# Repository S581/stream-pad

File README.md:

# Steampad ⌨️

**Steampad** is a high-performance 4x4 macropad featuring a rotary encoder and full per-key RGB lighting. Powered by the **Seeed Studio XIAO RP2040**, it is designed for maximum productivity and customization using **QMK Firmware** and the **VIAL** protocol.

---

## Features
* **16 Mechanical Keys:** A full 4x4 grid for macros, shortcuts, and numpad use.
* **Rotary Encoder:** EC11 encoder for precision volume control, scrolling, or scrubbing.
* **Per-Key RGB:** 16 integrated SK6812 Mini-E LEDs for vibrant, customizable lighting.
* **VIAL Support:** Change your keymap and macros in real-time via the VIAL web or desktop app—no code editing required after flashing.
* **RP2040 Power:** Utilizes the RP2040's PIO state machines for perfect LED timing and ultra-low latency.

---

## Hardware Overview
The Steampad uses a matrix circuit with a **COL2ROW** diode orientation, ensuring that every keypress is registered independently (NKRO). Designed in KiCad.

### PCB & Pinout
* **Controller:** Seeed Studio XIAO RP2040
* **Rows:** GP0, GP1, GP2, GP3
* **Columns:** GP4, GP7, GP27, GP26
* **RGB Data:** GP6 (D5)
* **Encoder:** GP29 (Phase A), GP28 (Phase B)

---

---

## Firmware Overview
The firmware is built on **QMK** with VIAL features enabled. 

### Default Keymap:
* **Row 0:** Chrome, Discord, File Explorer, Next Track
* **Row 1:** Ctrl+Alt+Del, Copy, Paste, Previous Track
* **Row 2:** Lock Computer, Snipping Tool, Game Bar, Windows+Tab
* **Row 3:** Undo (Ctrl+Z), Win+E, Win+D, Play/Pause (Encoder Click)
* **Encoder Rotation:** Volume Up / Volume Down

### VIAL Customization:
1. Flash the `.uf2` file.
2. Visit [vial.rocks](https://vial.rocks).
3. Connect your Steampad to remap keys and create macros instantly.

---

## BOM (Bill of Materials)
* **1x** Seeed XIAO RP2040
* **1x** EC11 Rotary Encoder
* **16x** MX-style Mechanical Switches
* **16x** 1N4148 Diodes
* **16x** SK6812 Mini-E (or WS2812B) LEDs
* **16x** Keycaps
* **3x** M3x5mx4mm heatset inserts
* **1x** Steampad Case & Plate

---

### Others:
Hi, I made this for 2 days and this is my first time ever coding, making PCBs, and making cases in fusion. I have very little experience with softwares like Fusion and KiCad.
I made this MacroPad to make my life easier and also to gain experiences for my future career.

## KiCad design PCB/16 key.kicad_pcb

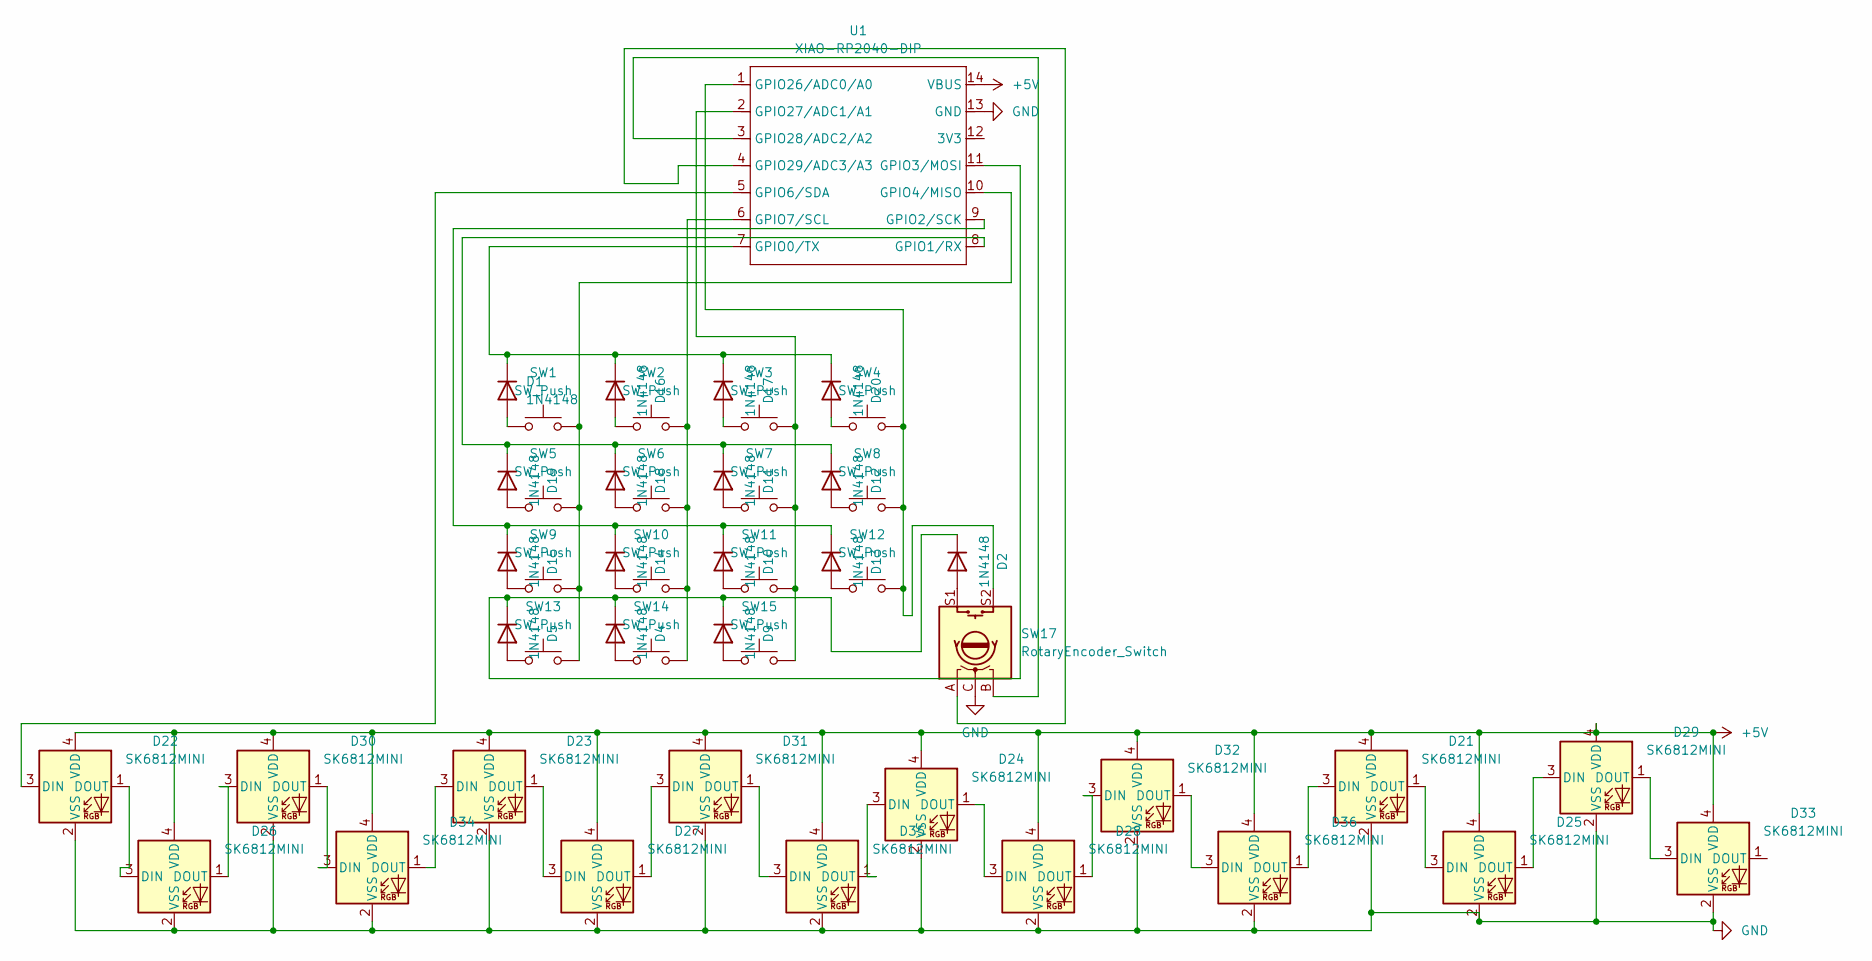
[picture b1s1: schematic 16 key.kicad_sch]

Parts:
D1, D2, D4, D5, D9, D10, D11, D12, D13, D14, D15, D16, D17, D18, D19, D20: 1N4148; D_DO-35_SOD27_P7.62mm_Horizontal
D21, D22, D23, D24, D25, D26, D27, D28, D29, D30, D31, D32, D33, D34, D35, D36: SK6812MINI; LED_SK6812MINI_PLCC4_3.5x3.5mm_P1.75mm
SW1, SW2, SW3, SW4, SW5, SW6, SW7, SW8, SW9, SW10, SW11, SW12, SW13, SW14, SW15: SW_Push; SW_Cherry_MX_1.00u_PCB
SW17: RotaryEncoder_Switch; RotaryEncoder_Alps_EC11E-Switch_Vertical_H20mm
U1: XIAO-RP2040-DIP

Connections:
+5V: D21.4 (VDD), D22.4 (VDD), D23.4 (VDD), D24.4 (VDD), D25.4 (VDD), D26.4 (VDD), D27.4 (VDD), D28.4 (VDD), D29.4 (VDD), D30.4 (VDD), D31.4 (VDD), D32.4 (VDD), D33.4 (VDD), D34.4 (VDD), D35.4 (VDD), D36.4 (VDD), U1.14 (VBUS)
GND: D21.2 (VSS), D22.2 (VSS), D23.2 (VSS), D24.2 (VSS), D25.2 (VSS), D26.2 (VSS), D27.2 (VSS), D28.2 (VSS), D29.2 (VSS), D30.2 (VSS), D31.2 (VSS), D32.2 (VSS), D33.2 (VSS), D34.2 (VSS), D35.2 (VSS), D36.2 (VSS), SW17.C, U1.13 (GND)
unnamed: D1.2 (A), SW1.1
unnamed: D1.1 (K), D16.1 (K), D17.1 (K), D20.1 (K), U1.7 (GPIO0/TX)
unnamed: D2.2 (A), SW17.S1
unnamed: D2.1 (K), D4.1 (K), D5.1 (K), D9.1 (K), U1.11 (GPIO3/MOSI)
unnamed: D4.2 (A), SW14.1
unnamed: D5.2 (A), SW13.1
unnamed: D9.2 (A), SW15.1
unnamed: D10.2 (A), SW11.1
unnamed: D10.1 (K), D13.1 (K), D14.1 (K), D15.1 (K), U1.9 (GPIO2/SCK)
unnamed: D11.2 (A), SW7.1
unnamed: D11.1 (K), D12.1 (K), D18.1 (K), D19.1 (K), U1.8 (GPIO1/RX)
unnamed: D12.2 (A), SW8.1
unnamed: D13.2 (A), SW12.1
unnamed: D14.2 (A), SW10.1
unnamed: D15.2 (A), SW9.1
unnamed: D16.2 (A), SW2.1
unnamed: D17.2 (A), SW3.1
unnamed: D18.2 (A), SW6.1
unnamed: D19.2 (A), SW5.1
unnamed: D20.2 (A), SW4.1
unnamed: D21.3 (DIN), D36.1 (DOUT)
unnamed: D21.1 (DOUT), D25.3 (DIN)
unnamed: D22.3 (DIN), U1.5 (GPIO6/SDA)
unnamed: D22.1 (DOUT), D26.3 (DIN)
unnamed: D23.3 (DIN), D34.1 (DOUT)
unnamed: D23.1 (DOUT), D27.3 (DIN)
unnamed: D24.3 (DIN), D35.1 (DOUT)
unnamed: D24.1 (DOUT), D28.3 (DIN)
unnamed: D25.1 (DOUT), D29.3 (DIN)
unnamed: D26.1 (DOUT), D30.3 (DIN)
unnamed: D27.1 (DOUT), D31.3 (DIN)
unnamed: D28.1 (DOUT), D32.3 (DIN)
unnamed: D29.1 (DOUT), D33.3 (DIN)
unnamed: D30.1 (DOUT), D34.3 (DIN)
unnamed: D31.1 (DOUT), D35.3 (DIN)
unnamed: D32.1 (DOUT), D36.3 (DIN)
unnamed: SW1.2, SW5.2, SW9.2, SW13.2, U1.10 (GPIO4/MISO)
unnamed: SW2.2, SW6.2, SW10.2, SW14.2, U1.6 (GPIO7/SCL)
unnamed: SW4.2, SW8.2, SW12.2, SW17.S2, U1.1 (GPIO26/ADC0/A0)
unnamed: SW3.2, SW7.2, SW11.2, SW15.2, U1.2 (GPIO27/ADC1/A1)
unnamed: SW17.B, U1.3 (GPIO28/ADC2/A2)
unnamed: SW17.A, U1.4 (GPIO29/ADC3/A3)

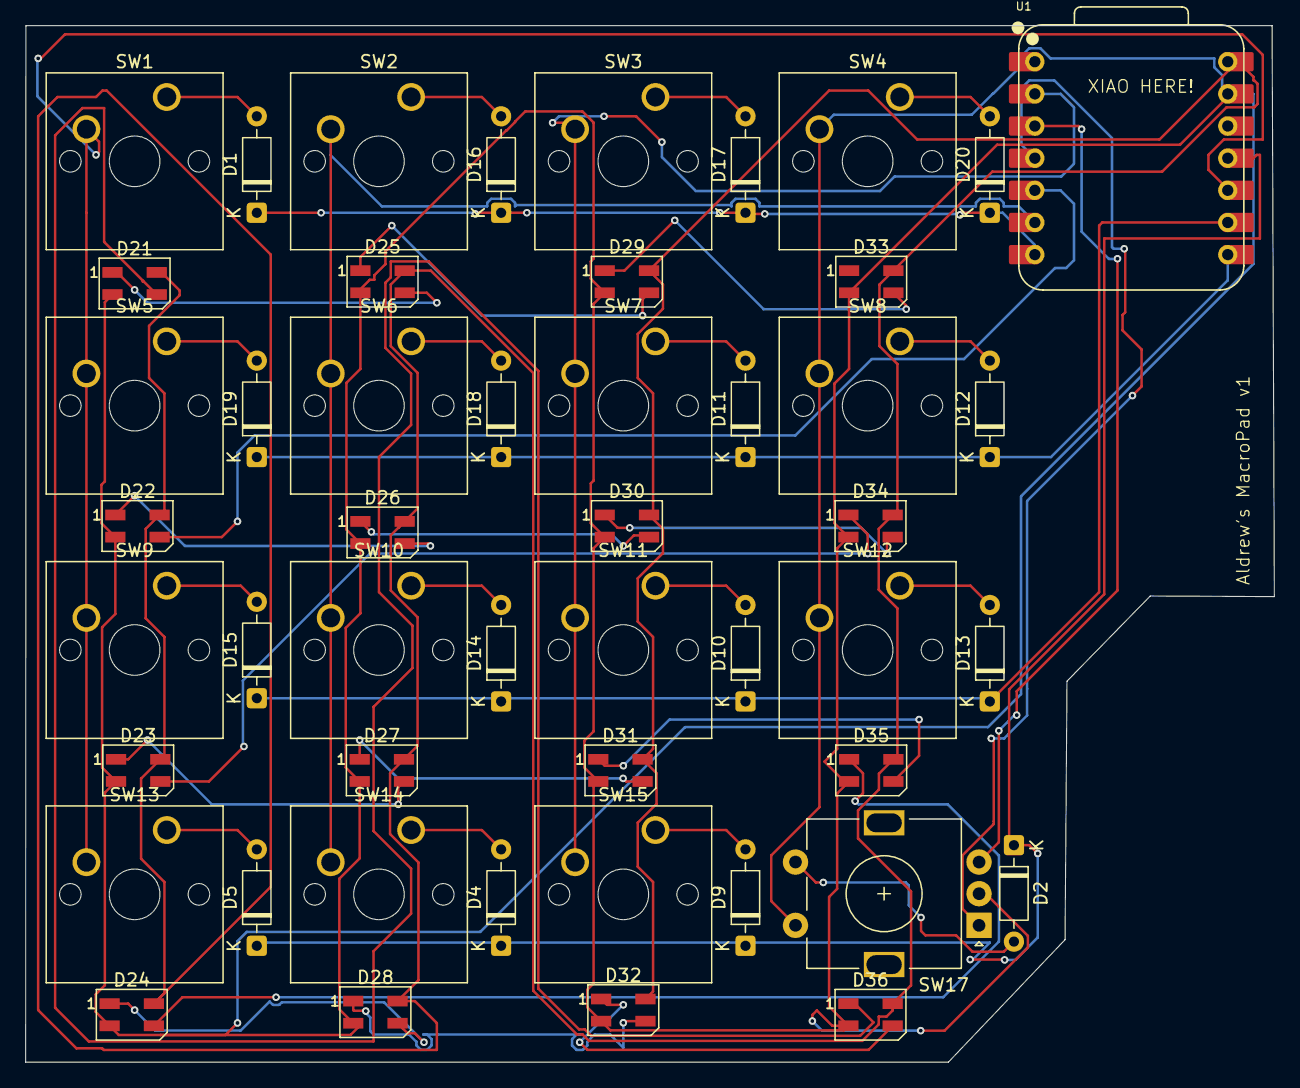
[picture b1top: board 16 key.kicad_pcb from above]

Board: 2 copper layers, 98.7 x 81.9 mm, 49 parts (0 on the bottom side), 44 nets.

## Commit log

2025-12-24 Rename Screenshot 2025-12-24 123729.png to HackPad
2025-12-24 Rename Screenshot 2025-12-24 164010.png to PCB
2025-12-24 Rename HackPad to HackPad.png
2025-12-24 Rename PCB to PCB.png
2025-12-24 Rename Screenshot 2025-12-24 164025.png to schem.png
2025-12-24 Rename Screenshot 2025-12-24 164313.png to Case.png
